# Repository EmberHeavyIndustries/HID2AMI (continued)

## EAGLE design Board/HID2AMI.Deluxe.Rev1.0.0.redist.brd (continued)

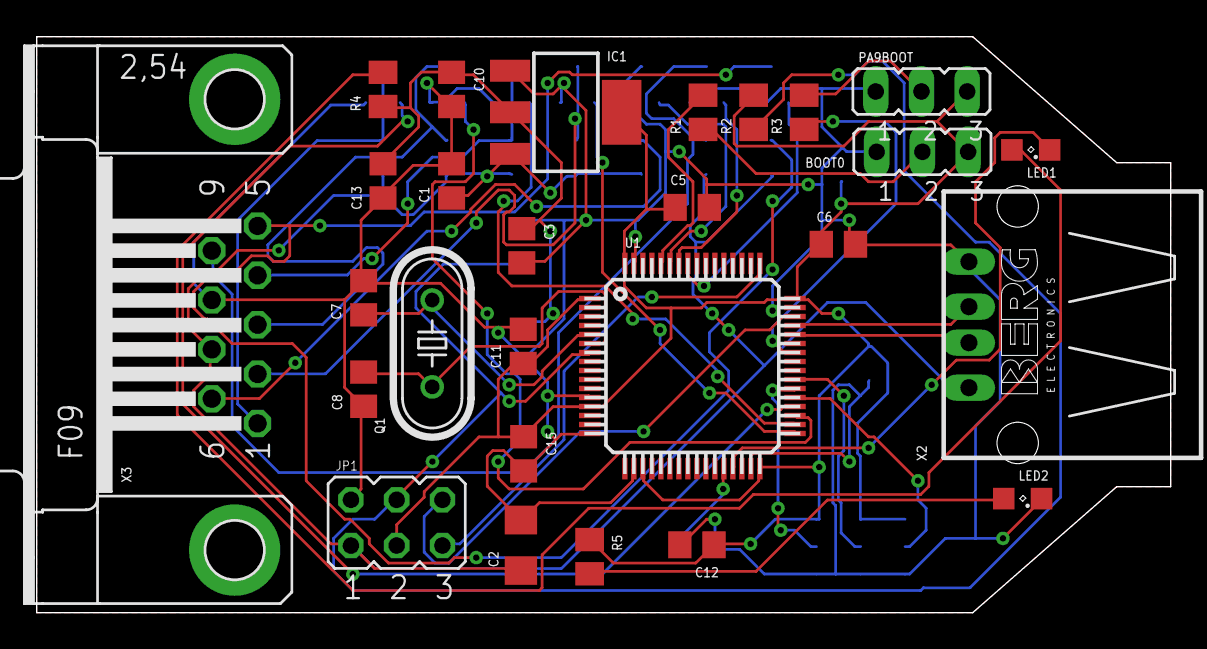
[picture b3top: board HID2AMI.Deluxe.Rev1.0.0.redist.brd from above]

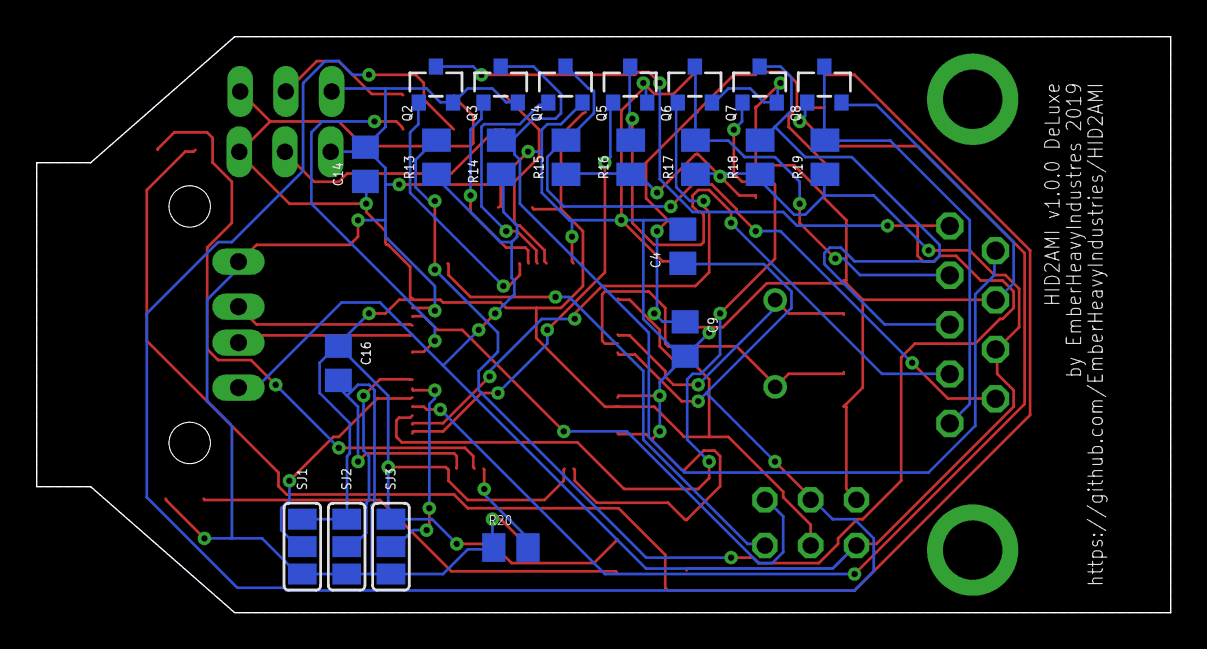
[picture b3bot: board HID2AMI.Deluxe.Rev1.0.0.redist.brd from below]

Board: 2 copper layers, 63.0 x 32.0 mm, 49 parts (22 on the bottom side), 35 nets.

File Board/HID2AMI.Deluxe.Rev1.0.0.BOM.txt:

|Part   |   Value  |     Device       |  Package   | Rev 1.0  |
|-------|--------- |------------------|------------|----------|
|BOOT0  |   JP2E   |        JP1       |   JUMPER   |          |
|PA9BOOT|   JP2E   |        JP2       |   JUMPER   |          |
|       |          |                  |            |          |
|C1     | 100n     |   C-EUC0805      |  C0805     | Optional |
|C2     | 10u      |   C-EUC1206      |  C1206     | Optional |
|C3     | 100n     |   C-EUC0805      |  C0805     | Optional |
|C4     | 100n     |   C-EUC0805      |  C0805     | Optional |
|C5     | 100n     |   C-EUC0805      |  C0805     | MANDATORY|
|C6     | 100n     |   C-EUC0805      |  C0805     | MANDATORY|
|C7     | 22p      |   C-EUC0805      |  C0805     | MANDATORY|
|C8     | 22p      |   C-EUC0805      |  C0805     | MANDATORY|
|C9     | 100n     |   C-EUC0805      |  C0805     | Optional |
|C10    | 10u      |   C-EUC1206      |  C1206     | Optional |
|C11    | 100n     |   C-EUC0805      |  C0805     | MANDATORY|
|C12    | 100n     |   C-EUC0805      |  C0805     | MANDATORY|
|C13    | 100n     |   C-EUC0805      |  C0805     | Optional |
|C14    | 100n     |   C-EUC0805      |  C0805     | Optional |
|C15    | 100n     |   C-EUC0805      |  C0805     | Optional |
|C16    | 100n     |   C-EUC0805      |  C0805     | Optional |
|       |          |                  |            |          |
|IC1    |LM1117-3.3|   LM1117MPX-3.3  |  SOT223    | MANDATORY|
|       |          |                  |            |          |
|LED1   |          |   LEDSML0805     |  SML0805   | Optional |
|LED2   |          |   LEDSML0805     |  SML0805   | Optional |
|       |          |                  |            |          |
|Q1     | 8MHz     |   CRYSTALHC49S   |  HC49/S    | MANDATORY|
|       |          |                  |            |          |
|Q2     | BSS138   |   BSS138         |  SOT23     | MANDATORY|
|Q3     | BSS138   |   BSS138         |  SOT23     | MANDATORY|
|Q4     | BSS138   |   BSS138         |  SOT23     | MANDATORY|
|Q5     | BSS138   |   BSS138         |  SOT23     | MANDATORY|
|Q6     | BSS138   |   BSS138         |  SOT23     | MANDATORY|
|Q7     | BSS138   |   BSS138         |  SOT23     | MANDATORY|
|Q8     | BSS138   |   BSS138         |  SOT23     | MANDATORY|
|       |          |                  |            |          |
|R1     | 0k       |   SHORT          |  M805      | MANDATORY|
|R2     | 100k     |   R-EU_M0805     |  M805      | MANDATORY|
|R3     | 0k       |   SHORT          |  M805      | MANDATORY|
|R4     | 1k-10k   |   R-EU_M0805     |  M805      | Optional |
|R5     | 1k-10k   |   R-EU_M0805     |  M805      | Optional |
|R6-R12 | ---      |   --             |  --        | NA       |
|R13    | 100k     |   R-EU_M0805     |  M805      | MANDATORY|
|R14    | 100k     |   R-EU_M0805     |  M805      | MANDATORY|
|R15    | 100k     |   R-EU_M0805     |  M805      | MANDATORY|
|R16    | 100k     |   R-EU_M0805     |  M805      | MANDATORY|
|R17    | 100k     |   R-EU_M0805     |  M805      | MANDATORY|
|R18    | 100k     |   R-EU_M0805     |  M805      | MANDATORY|
|R19    | 100k     |   R-EU_M0805     |  M805      | MANDATORY|
|R20    | 0k       |   SHORT          |  M805      | MANDATORY|
|       |          |                  |            |          |
|U1     | F105RBT6 |   STM32F105RBT6  |  LQFP64    | MANDATORY|
|       |          |                  |            |          |
|X1     |          |   USB-CONNECTOR  |            | MANDATORY|
|X3     |          |   F09HP D-SUB9   |  F09HP     | MANDATORY|
|       |          |                  |            |          |

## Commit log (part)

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2019-02-11 Create x
2021-01-21 Update README.md
    Fixed typo
2025-12-25 Fix formatting in README.md for features section
2026-02-05 Improve formatting of personality table in README
    Updated the personality table formatting for clarity.
2026-02-05 Fix formatting in personality table in README.md
2026-02-05 Update personality table formatting in README
2026-02-05 Fix personality table header from W1 to SW1
    Updated personality table header to correct switch labeling.
2026-02-05 Revise personality table format in README
    Updated personality switch positions and notes format in the README.
